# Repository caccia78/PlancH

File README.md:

# PlancH

**A desk button panel for Home Assistant.** Ten tactile buttons, a small OLED display, a touch
area and thirteen addressable RGB LEDs on a black PCB that sits on your desk, either on its own
rubber feet or on a 3D-printed stand. Powered by a Waveshare ESP32-S3-Zero running
[ESPHome](https://esphome.io), with native Home Assistant integration.

**📖 Documentation: [caccia78.github.io/PlancH](https://caccia78.github.io/PlancH/)**

https://github.com/user-attachments/assets/e7710835-a2c8-45fb-a4f4-b32c819555f0

*The video is also in [`media/`](media/) (MP4 and WebM).*

> **Status: Rev. 1, prototypes on order.** The design is complete and passes ERC/DRC, but the
> first boards have not been assembled and tested yet. Build one if you like to tinker, and
> expect changes.

## Features

- **10 tactile buttons**: a directional pad (up, down, left, right, OK), Back, and four scene buttons.
- **0.96" OLED display** (SSD1306, 128 × 64, white) for menus and feedback.
- **Capacitive touch area** on the top "ear" to wake the display.
- **13 addressable RGB LEDs** (SK6812): 3 status LEDs, 4 scene LEDs shining through milled
  windows in the PCB, and 6 backlight LEDs that light up the desk underneath.
- **Waveshare ESP32-S3-Zero** module, powered and programmed over USB-C.
- **Hand-solderable**: no parts with contacts under the body, passives 0805 or larger.
- **ESPHome firmware** with native Home Assistant API.
- **Accessories**: a 3D-printed desk stand, with more to come.

| Front | Back |
| --- | --- |
|  |  |

## Build your own

1. **Order the PCB.** Upload `production/gerber/` (or the Gerber ZIP attached to the
   [latest release](../../releases/latest)) to JLCPCB, PCBWay or any other maker.
   Reference settings: 2 layers, 2.0 mm FR4 (1.6 mm works too), matte black solder mask,
   white silkscreen, ENIG finish.
2. **Get the components.** The bill of materials is in
   [`production/planch-bom.csv`](production/planch-bom.csv), with manufacturer part numbers.
3. **Solder.** Open [`production/planch-ibom.html`](production/planch-ibom.html) in a browser:
   the interactive BOM highlights every part on the board. Suggested order: passives and LEDs
   on the back, buttons, ESP32 module, OLED last.
4. **Flash the firmware.** Run `esphome run firmware/planch.yaml` and set the Wi-Fi after
   flashing. Then install the Home Assistant package `homeassistant/planch.yaml` and put the
   label **PlancH** on the devices to control: the panel finds them by itself, by room.
5. **Print a stand** (optional): the [desk stand](mechanical/desk-stand/README.md) or the
   magnetic [wall mount](mechanical/wall-mount/README.md), with ready-to-print 3MF and STL files.

The [project website](https://caccia78.github.io/PlancH/) has the full documentation:
[components with shop links](https://caccia78.github.io/PlancH/build/components/),
[PCB ordering](https://caccia78.github.io/PlancH/build/ordering/), a step-by-step
[assembly guide](https://caccia78.github.io/PlancH/build/assembly/),
[firmware](https://caccia78.github.io/PlancH/firmware/) and
[Home Assistant](https://caccia78.github.io/PlancH/home-assistant/) setup.

## Repository layout

```
hardware/      KiCad 10 project: schematic, PCB, custom symbols, footprints and 3D models
production/    Gerber and drill files, BOM, pick-and-place, interactive BOM, schematic PDF, STEP
mechanical/    3D-printable accessories (build123d sources, STL, 3MF, STEP)
firmware/      ESPHome: planch.yaml (board), planch-bringup.yaml (assembly test), planch-test.yaml (test bench)
homeassistant/ Home Assistant package (menu from labels and areas) and test bench dashboard
media/         renders and video
```

## License

PlancH is open source hardware.

- **Hardware** (KiCad sources, production files, 3D-printed accessories):
  [CERN-OHL-S v2](LICENSES/CERN-OHL-S-2.0.txt)
- **Firmware and scripts**: [MIT](LICENSES/MIT.txt)
- **Documentation, renders and video**: [CC BY-SA 4.0](LICENSES/CC-BY-SA-4.0.txt)

See [LICENSE.md](LICENSE.md) for details. The source location printed on the back of the board
is `github.com/caccia78/planch`.

© 2026 Vincenzo Cacciatore

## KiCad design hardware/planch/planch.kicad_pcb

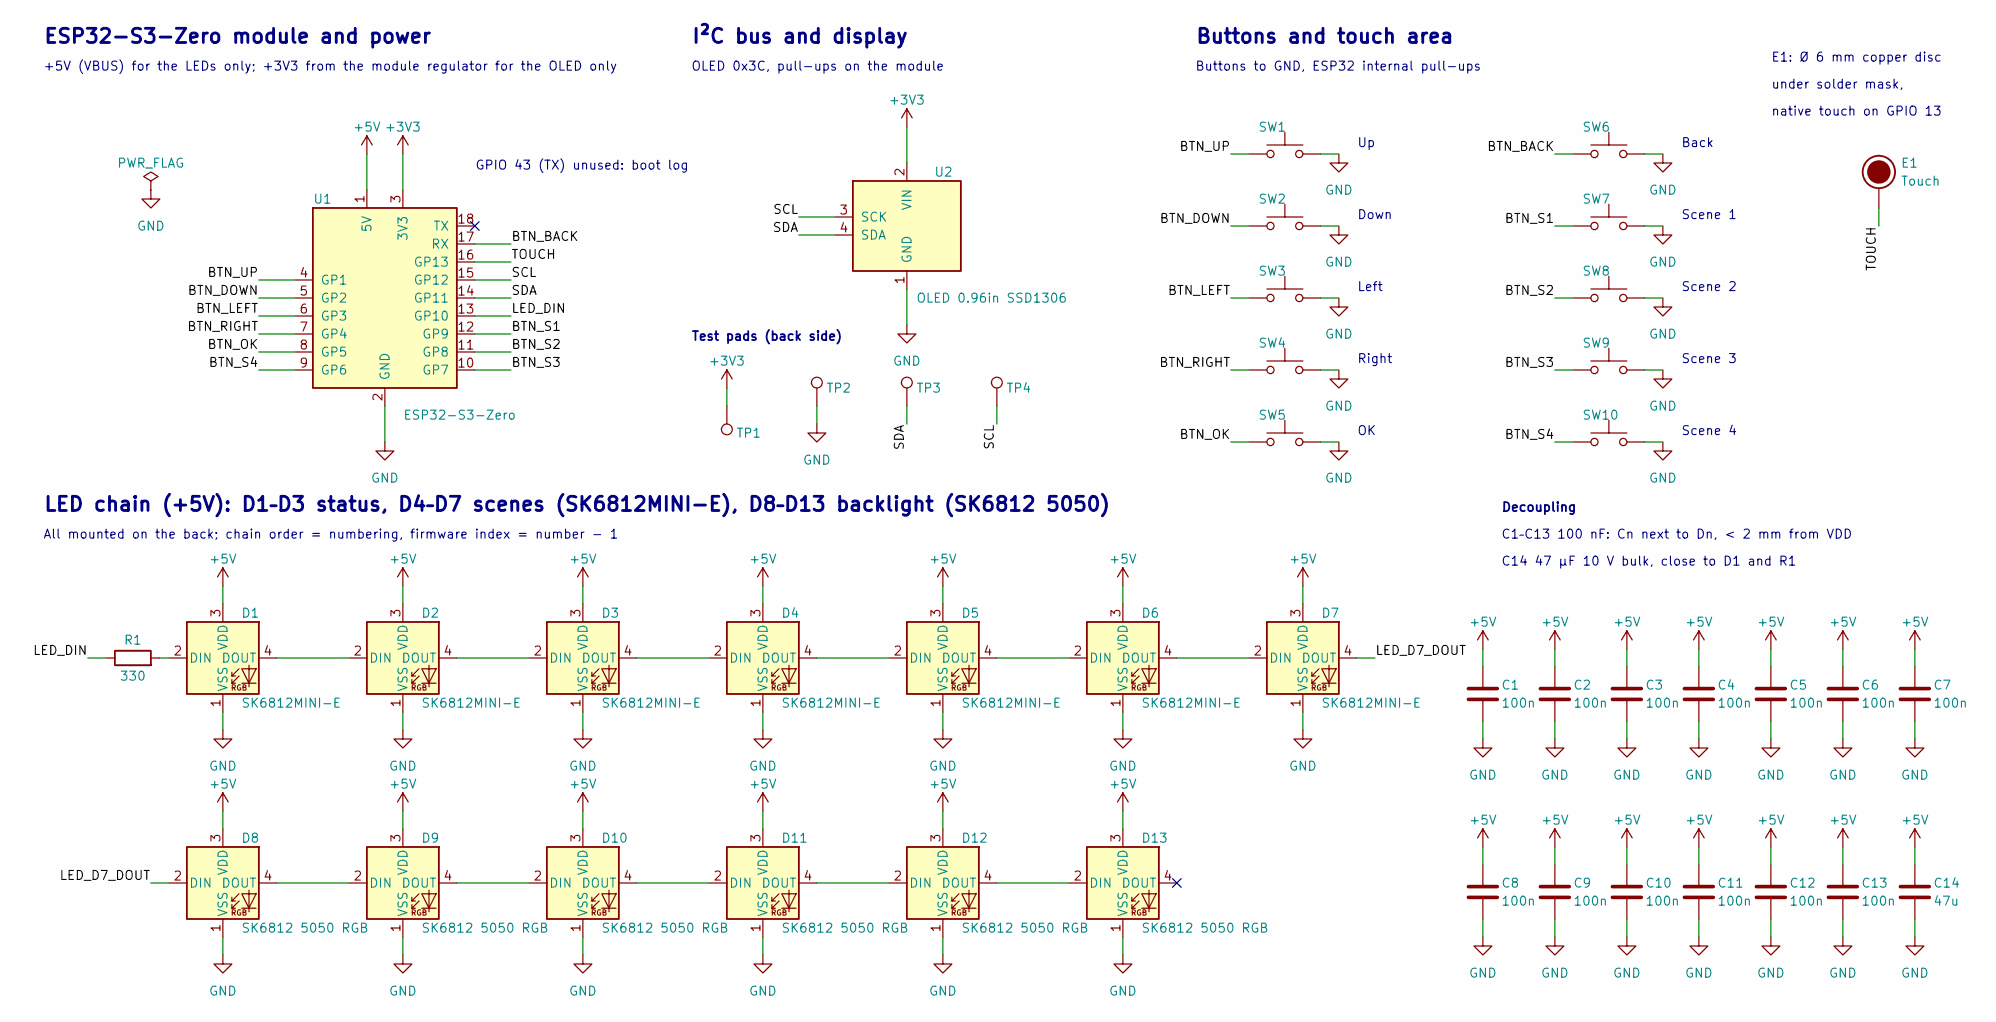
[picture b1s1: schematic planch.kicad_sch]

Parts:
C1, C2, C3, C4, C5, C6, C7, C8, C9, C10, C11, C12, C13: 100n; C_0805_2012Metric_Pad1.18x1.45mm_HandSolder; MPN CL21B104KBCNNNC
C14: 47u; C_1206_3216Metric_Pad1.33x1.80mm_HandSolder; MPN CL31A476MPHNNNE
D1, D2, D3, D4, D5, D6, D7: SK6812MINI-E; LED_SK6812MINI-E_3.2x2.8mm_P1.5mm_ReverseMount_HandSolder; MPN SK6812MINI-E
D8, D9, D10, D11, D12, D13: SK6812 5050 RGB; LED_SK6812_PLCC4_5.0x5.0mm_P3.2mm; MPN SKC6812RV
E1: Touch; TouchPad_D6mm_Covered
R1: 330; R_0805_2012Metric_Pad1.20x1.40mm_HandSolder; MPN RC0805FR-07330RL
SW1, SW2, SW3, SW4, SW5, SW6, SW7, SW8, SW9, SW10: PTS645SH43; SW_SPST_PTS645Sx43SMTR92_NoSilk; MPN PTS645SH43SMTR92 LFS
TP1: 3V3; TestPoint_Pad_D1.5mm
TP2: GND; TestPoint_Pad_D1.5mm
TP3: SDA; TestPoint_Pad_D1.5mm
TP4: SCL; TestPoint_Pad_D1.5mm
U1: ESP32-S3-Zero; Waveshare_ESP32-S3-Zero_Castellated; MPN ESP32-S3-Zero
U2: OLED 0.96in SSD1306; OLED_SSD1306_0.96in_I2C_24.8x26.9mm; MPN SSD1306 0.96in I2C module

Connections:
+3V3: TP1.1 (1_1), U1.3 (3V3), U2.2 (VIN)
+5V: C1.1, C2.1, C3.1, C4.1, C5.1, C6.1, C7.1, C8.1, C9.1, C10.1, C11.1, C12.1, C13.1, C14.1, D1.3 (VDD), D2.3 (VDD), D3.3 (VDD), D4.3 (VDD), D5.3 (VDD), D6.3 (VDD), D7.3 (VDD), D8.3 (VDD), D9.3 (VDD), D10.3 (VDD), D11.3 (VDD), D12.3 (VDD), D13.3 (VDD), U1.1 (5V)
/BTN_BACK: SW6.1, U1.17 (RX)
/BTN_DOWN: SW2.1, U1.5 (GP2)
/BTN_LEFT: SW3.1, U1.6 (GP3)
/BTN_OK: SW5.1, U1.8 (GP5)
/BTN_RIGHT: SW4.1, U1.7 (GP4)
/BTN_S1: SW7.1, U1.12 (GP9)
/BTN_S2: SW8.1, U1.11 (GP8)
/BTN_S3: SW9.1, U1.10 (GP7)
/BTN_S4: SW10.1, U1.9 (GP6)
/BTN_UP: SW1.1, U1.4 (GP1)
/LED_D7_DOUT: D7.4 (DOUT), D8.2 (DIN)
/LED_DIN: R1.1, U1.13 (GP10)
/SCL: TP4.1 (1_1), U1.15 (GP12), U2.3 (SCK)
/SDA: TP3.1 (1_1), U1.14 (GP11), U2.4 (SDA)
/TOUCH: E1.1, U1.16 (GP13)
GND: C1.2, C2.2, C3.2, C4.2, C5.2, C6.2, C7.2, C8.2, C9.2, C10.2, C11.2, C12.2, C13.2, C14.2, D1.1 (VSS), D2.1 (VSS), D3.1 (VSS), D4.1 (VSS), D5.1 (VSS), D6.1 (VSS), D7.1 (VSS), D8.1 (VSS), D9.1 (VSS), D10.1 (VSS), D11.1 (VSS), D12.1 (VSS), D13.1 (VSS), SW1.2, SW2.2, SW3.2, SW4.2, SW5.2, SW6.2, SW7.2, SW8.2, SW9.2, SW10.2, TP2.1 (1_1), U1.2 (GND), U2.1 (GND)
unnamed: D1.2 (DIN), R1.2
unnamed: D1.4 (DOUT), D2.2 (DIN)
unnamed: D2.4 (DOUT), D3.2 (DIN)
unnamed: D3.4 (DOUT), D4.2 (DIN)
unnamed: D4.4 (DOUT), D5.2 (DIN)
unnamed: D5.4 (DOUT), D6.2 (DIN)
unnamed: D6.4 (DOUT), D7.2 (DIN)
unnamed: D8.4 (DOUT), D9.2 (DIN)
unnamed: D9.4 (DOUT), D10.2 (DIN)
unnamed: D10.4 (DOUT), D11.2 (DIN)
unnamed: D11.4 (DOUT), D12.2 (DIN)
unnamed: D12.4 (DOUT), D13.2 (DIN)

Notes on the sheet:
ESP32-S3-Zero module and power
+5V (VBUS) for the LEDs only; +3V3 from the module regulator for the OLED only
GPIO 43 (TX) unused: boot log
I²C bus and display
OLED 0x3C, pull-ups on the module
Test pads (back side)
Buttons and touch area
Buttons to GND, ESP32 internal pull-ups
Down
Left
Right
Back
Scene 1
Scene 2
Scene 3
Scene 4
E1: Ø 6 mm copper disc
under solder mask,
native touch on GPIO 13
LED chain (+5V): D1–D3 status, D4–D7 scenes (SK6812MINI-E), D8–D13 backlight (SK6812 5050)
All mounted on the back; chain order = numbering, firmware index = number − 1
Decoupling
C1–C13 100 nF: Cn next to Dn, < 2 mm from VDD
C14 47 µF 10 V bulk, close to D1 and R1

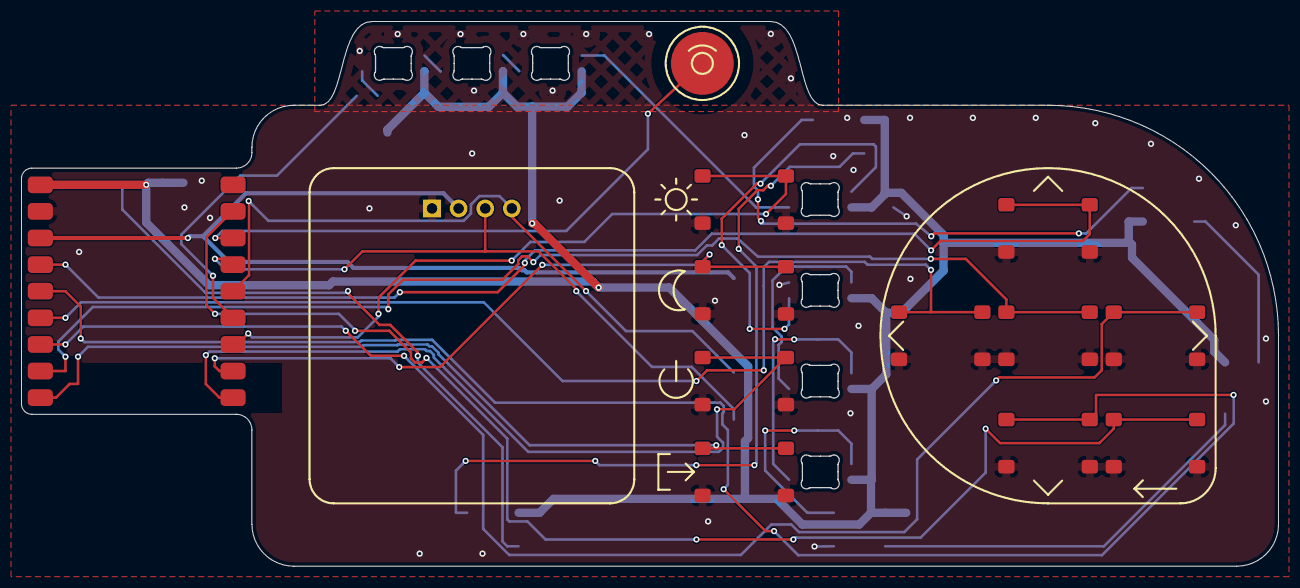
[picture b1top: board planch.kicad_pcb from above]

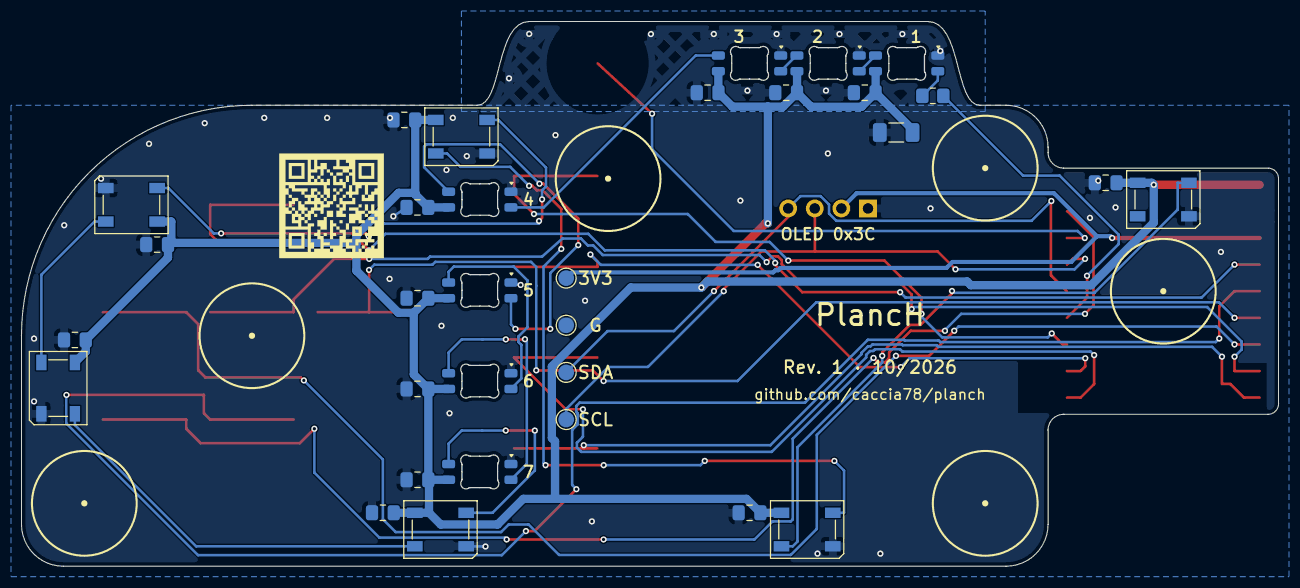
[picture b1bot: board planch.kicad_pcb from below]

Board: 2 copper layers, 120.0 x 52.0 mm, 45 parts (32 on the bottom side), 30 nets.

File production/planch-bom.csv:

"Reference","Value","Footprint","Manufacturer","MPN","LCSC","Qty"
"C1-C13","100n","Capacitor_SMD:C_0805_2012Metric_Pad1.18x1.45mm_HandSolder","Samsung","CL21B104KBCNNNC","","13"
"C14","47u","Capacitor_SMD:C_1206_3216Metric_Pad1.33x1.80mm_HandSolder","Samsung","CL31A476MPHNNNE","","1"
"D1-D7","SK6812MINI-E","planch:LED_SK6812MINI-E_3.2x2.8mm_P1.5mm_ReverseMount_HandSolder","Opsco","SK6812MINI-E","","7"
"D8-D13","SK6812 5050 RGB","LED_SMD:LED_SK6812_PLCC4_5.0x5.0mm_P3.2mm","Opsco","SKC6812RV","","6"
"R1","330","Resistor_SMD:R_0805_2012Metric_Pad1.20x1.40mm_HandSolder","Yageo","RC0805FR-07330RL","","1"
"SW1-SW10","PTS645SH43","planch:SW_SPST_PTS645Sx43SMTR92_NoSilk","C&K","PTS645SH43SMTR92 LFS","","10"
"U1","ESP32-S3-Zero","planch:Waveshare_ESP32-S3-Zero_Castellated","Waveshare","ESP32-S3-Zero","","1"
"U2","OLED 0.96in SSD1306","planch:OLED_SSD1306_0.96in_I2C_24.8x26.9mm","","SSD1306 0.96in I2C module","","1"
